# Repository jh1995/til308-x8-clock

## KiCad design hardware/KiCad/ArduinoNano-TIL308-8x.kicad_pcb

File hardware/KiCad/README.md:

KiCad 5 files. They use my own library of obsolete parts available in elsewhere in my GitHub area.

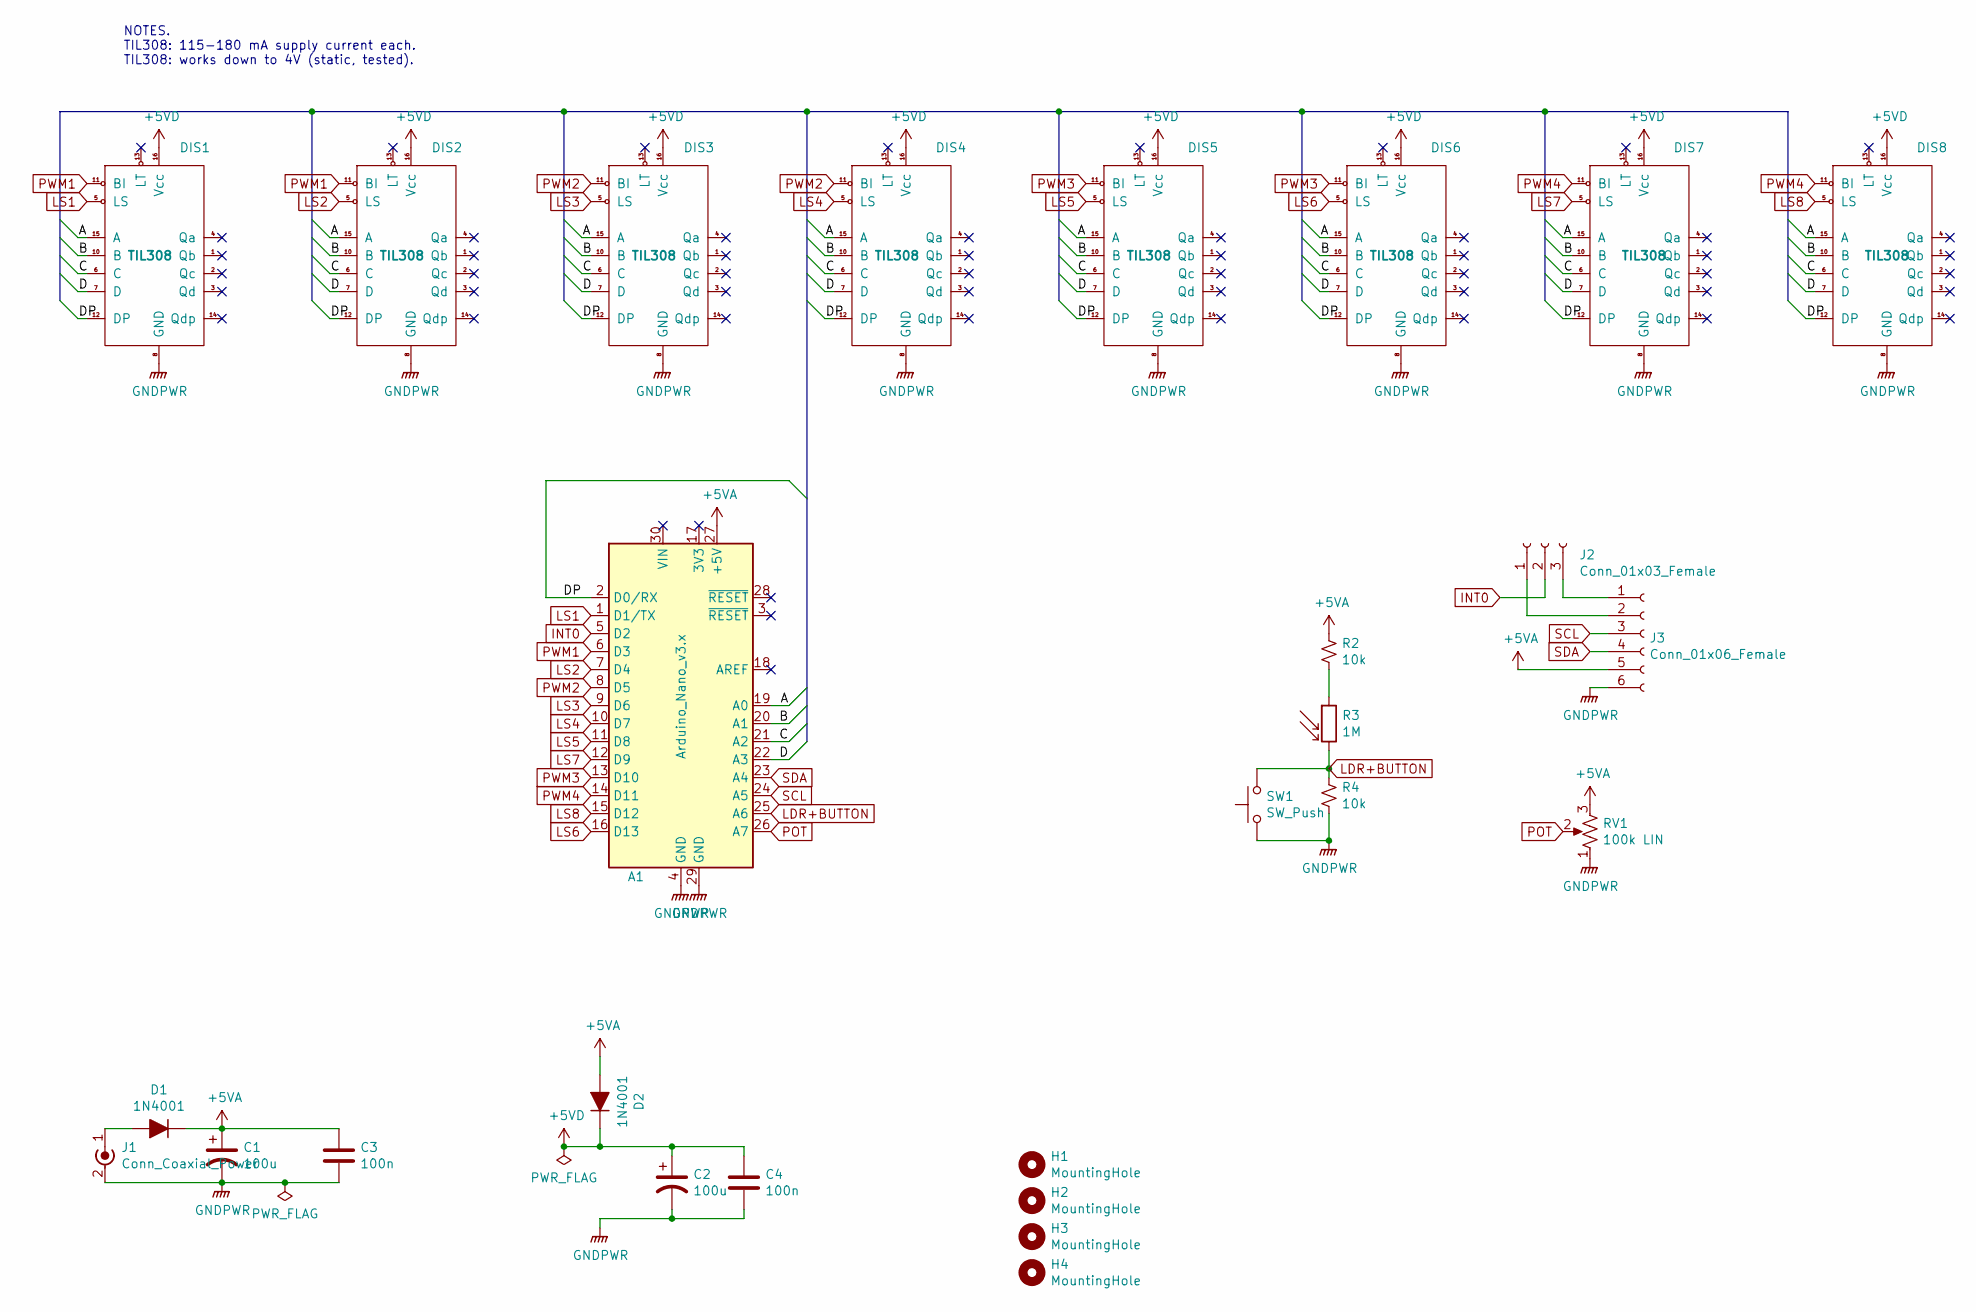
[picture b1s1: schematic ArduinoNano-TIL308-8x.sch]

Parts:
A1: Arduino_Nano_v3.x; Arduino_Nano
C1, C2: 100u; CP_Radial_D10.0mm_P5.00mm
C3, C4: 100n; C_Rect_L7.0mm_W2.5mm_P5.00mm
D1, D2: 1N4001; D_A-405_P7.62mm_Horizontal
DIS1, DIS2, DIS3, DIS4, DIS5, DIS6, DIS7, DIS8: TIL308
H1, H2, H3, H4: MountingHole; MountingHole_4.3mm_M4
J1: Conn_Coaxial_Power; Molex_KK-254_AE-6410-02A_1x02_P2.54mm_Vertical
J2: Conn_01x03_Female; SolderJumper-3_P1.3mm_Open_Pad1.0x1.5mm_NumberLabels
J3: Conn_01x06_Female; PinSocket_1x06_P2.54mm_Vertical
R2, R4: 10k; R_Axial_DIN0207_L6.3mm_D2.5mm_P2.54mm_Vertical
R3: 1M; PinSocket_1x02_P2.54mm_Vertical
RV1: 100k LIN; Molex_KK-254_AE-6410-03A_1x03_P2.54mm_Vertical
SW1: SW_Push; Molex_KK-254_AE-6410-02A_1x02_P2.54mm_Vertical

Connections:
+5VA: A1.27 (+5V), C1.1, C3.1, D1.1 (K), D2.2 (A), J3.5, R2.1, RV1.3
+5VD: C2.1, C4.1, D2.1 (K), DIS1.16 (Vcc), DIS2.16 (Vcc), DIS3.16 (Vcc), DIS4.16 (Vcc), DIS5.16 (Vcc), DIS6.16 (Vcc), DIS7.16 (Vcc), DIS8.16 (Vcc)
/A: A1.19 (A0), DIS1.15 (A), DIS2.15 (A), DIS3.15 (A), DIS4.15 (A), DIS5.15 (A), DIS6.15 (A), DIS7.15 (A), DIS8.15 (A)
/B: A1.20 (A1), DIS1.10 (B), DIS2.10 (B), DIS3.10 (B), DIS4.10 (B), DIS5.10 (B), DIS6.10 (B), DIS7.10 (B), DIS8.10 (B)
/C: A1.21 (A2), DIS1.6 (C), DIS2.6 (C), DIS3.6 (C), DIS4.6 (C), DIS5.6 (C), DIS6.6 (C), DIS7.6 (C), DIS8.6 (C)
/D: A1.22 (A3), DIS1.7 (D), DIS2.7 (D), DIS3.7 (D), DIS4.7 (D), DIS5.7 (D), DIS6.7 (D), DIS7.7 (D), DIS8.7 (D)
/DP: A1.2 (D0/RX), DIS1.12 (DP), DIS2.12 (DP), DIS3.12 (DP), DIS4.12 (DP), DIS5.12 (DP), DIS6.12 (DP), DIS7.12 (DP), DIS8.12 (DP)
GNDPWR: A1.4 (GND), A1.29 (GND), C1.2, C2.2, C3.2, C4.2, DIS1.8 (GND), DIS2.8 (GND), DIS3.8 (GND), DIS4.8 (GND), DIS5.8 (GND), DIS6.8 (GND), DIS7.8 (GND), DIS8.8 (GND), J1.2 (Ext), J3.6, R4.2, RV1.1, SW1.1
INT0: A1.5 (D2), J2.2
LDR+BUTTON: A1.25 (A6), R3.2, R4.1, SW1.2
LS1: A1.1 (D1/TX), DIS1.5 (LS)
LS2: A1.7 (D4), DIS2.5 (LS)
LS3: A1.9 (D6), DIS3.5 (LS)
LS4: A1.10 (D7), DIS4.5 (LS)
LS5: A1.11 (D8), DIS5.5 (LS)
LS6: A1.16 (D13), DIS6.5 (LS)
LS7: A1.12 (D9), DIS7.5 (LS)
LS8: A1.15 (D12), DIS8.5 (LS)
unnamed: D1.2 (A), J1.1 (In)
unnamed: J2.1, J3.2
unnamed: J2.3, J3.1
unnamed: R2.2, R3.1
POT: A1.26 (A7), RV1.2
PWM1: A1.6 (D3), DIS1.11 (BI), DIS2.11 (BI)
PWM2: A1.8 (D5), DIS3.11 (BI), DIS4.11 (BI)
PWM3: A1.13 (D10), DIS5.11 (BI), DIS6.11 (BI)
PWM4: A1.14 (D11), DIS7.11 (BI), DIS8.11 (BI)
SCL: A1.24 (A5), J3.3
SDA: A1.23 (A4), J3.4

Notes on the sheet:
NOTES. TIL308: 115-180 mA supply current each. TIL308: works down to 4V (static, tested).

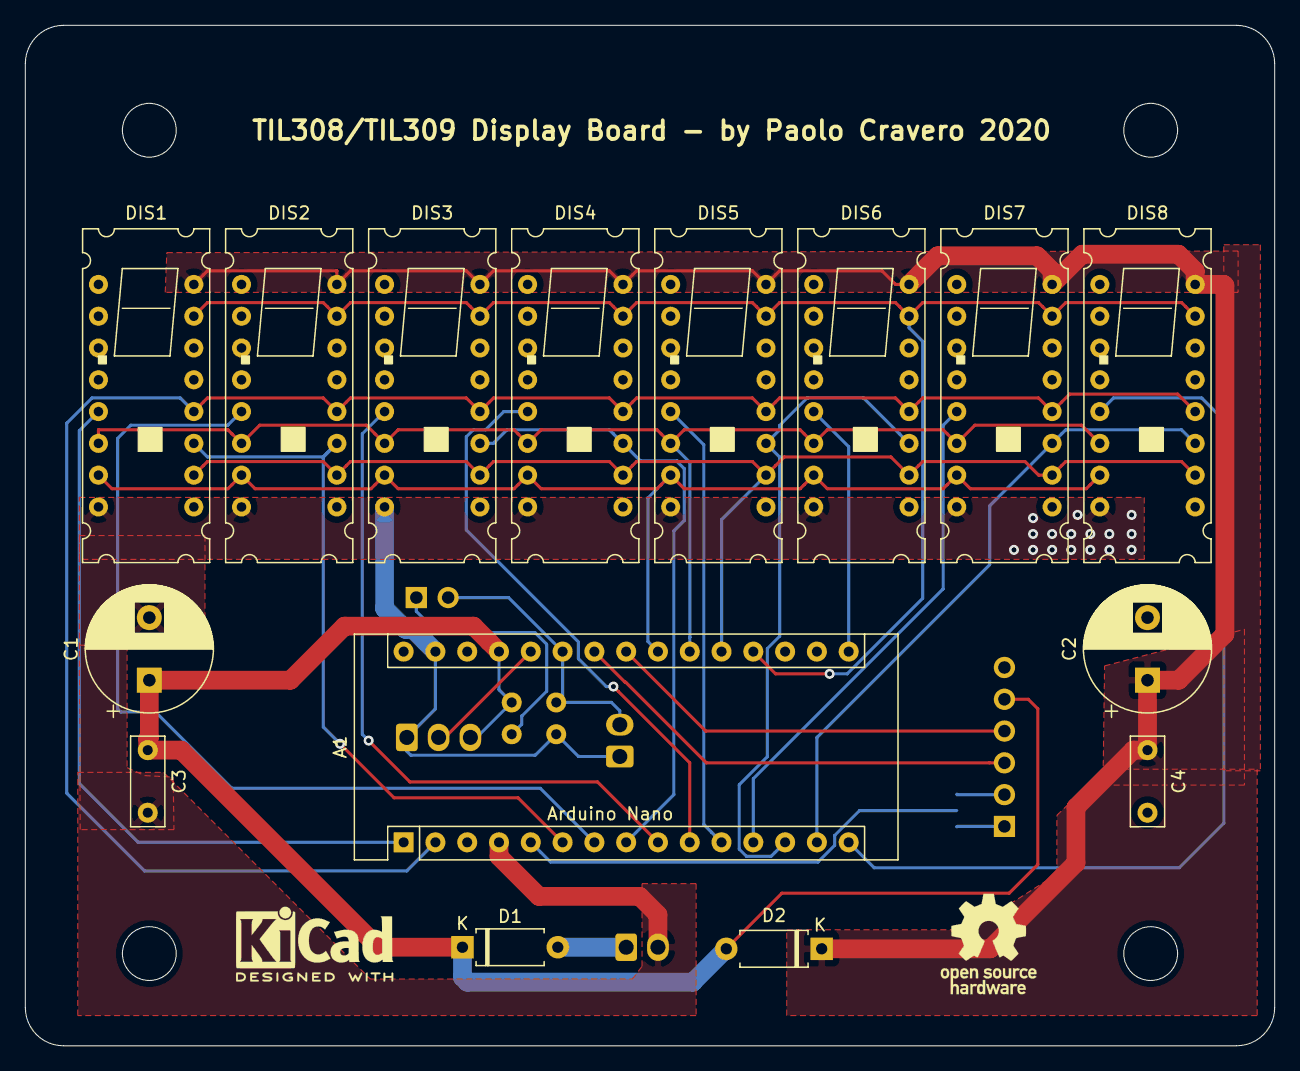
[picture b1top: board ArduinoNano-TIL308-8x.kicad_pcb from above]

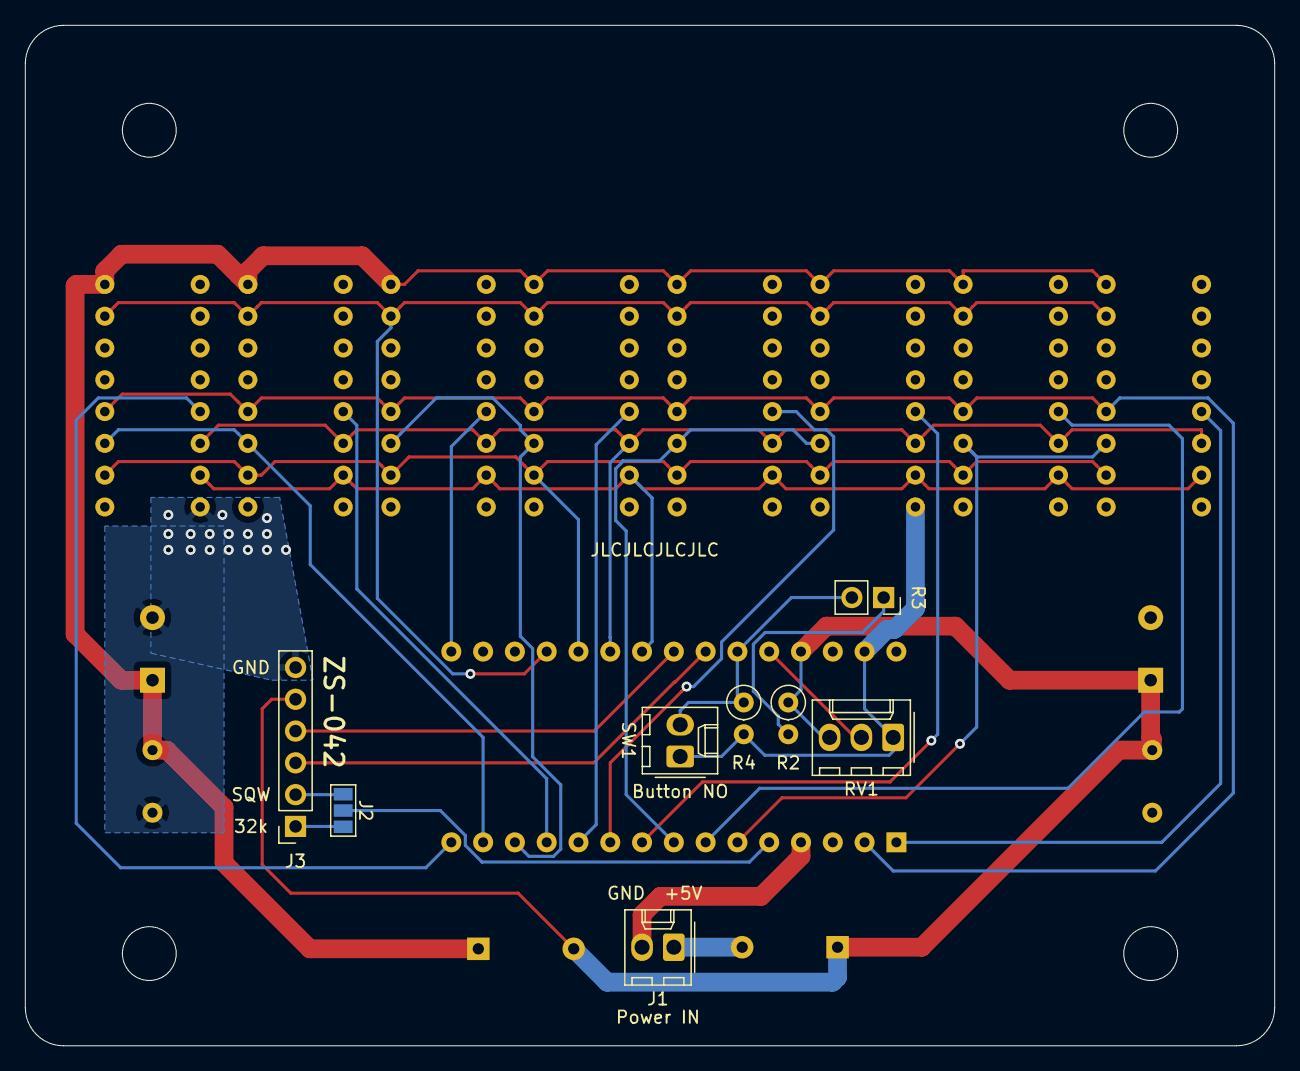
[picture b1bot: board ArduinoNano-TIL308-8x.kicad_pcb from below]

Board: 2 copper layers, 99.8 x 81.5 mm, 27 parts (8 on the bottom side), 29 nets.

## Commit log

2020-05-09 Files used to fab first PCB run
2020-06-06 First commit
    A crude but working sketch.
2020-09-19 Starting impl'ing a vector for displayed data
2020-09-21 displayVector and updateDisplayFromVector()
2020-12-22 +Display vector. +Time/Date set.
2020-12-26 +random words
2021-01-06 +dayOfWeek, fixes
    Added experimental display of day of the week. Bug fixes.
2021-01-09 Review of dayOfWeek display format
2021-01-17 Random seed now in EEPROM. Added new words.
